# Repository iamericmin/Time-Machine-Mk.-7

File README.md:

# Time-Machine-Mk.-7
Eagle files for the Time Machine Mk. 7, a DIY digital watch powered by a SAMD21 and an LIR2032 battery.

# Repo map
1. Cutting board: failed projects, simple mockups, etc. that didn't make it to the final product
2. Technical drawings: PDFs of TM7 Rev G, the final production version.
3. TM7 older versions: previous revisions of TM7 I kept just cuz

# This only contains hardware files, I'll be working and uploading software here as well soon!

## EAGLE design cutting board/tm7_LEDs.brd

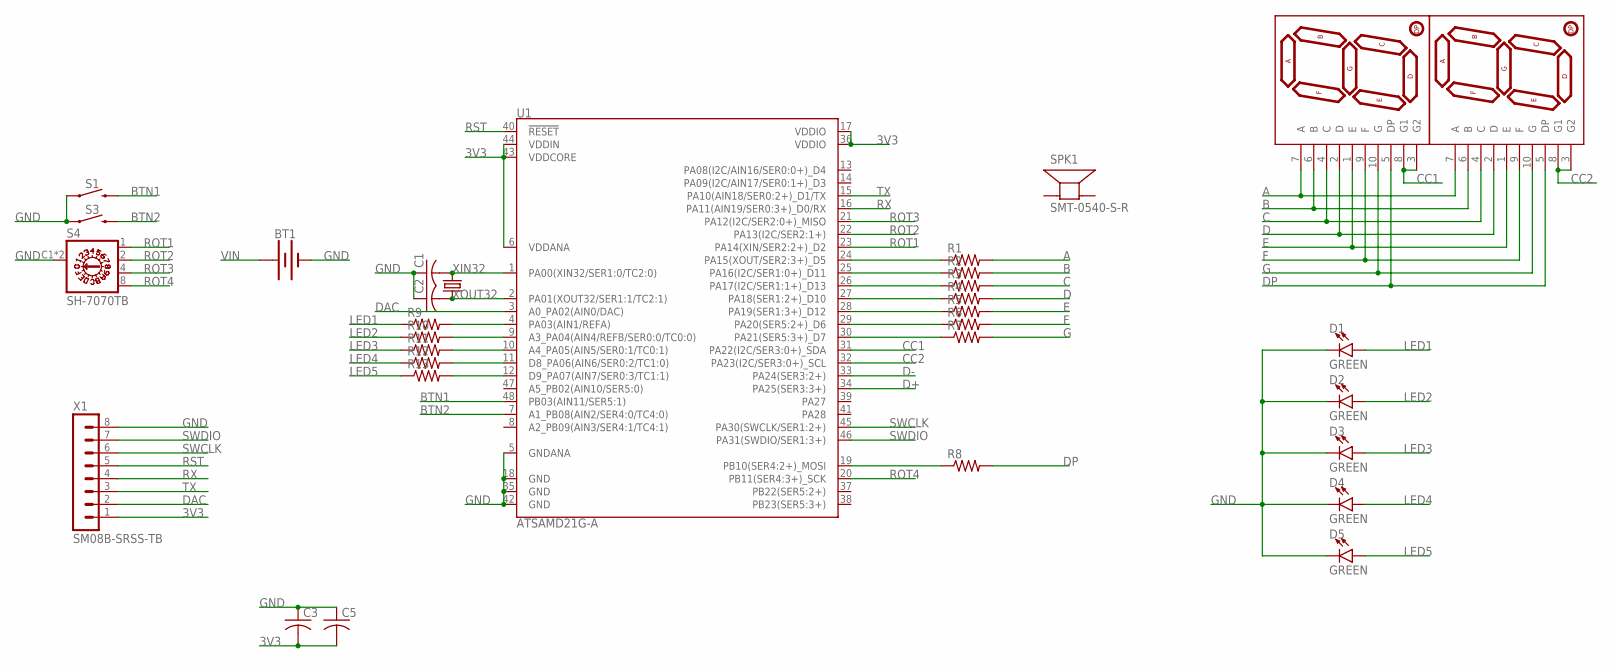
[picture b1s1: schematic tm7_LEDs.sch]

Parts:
BT1: BATTERY-20MM_SMD_4LEGS_OVERPASTE_INNER; BATTCON_20MM_4LEGS_OVERPASTE_INNER
C1, C2, C3, C5: C-USC0603; C0603
D1, D2, D3, D4, D5: GREEN; LED-1206
R1, R2, R3, R4, R5, R6, R7, R8, R9, R10, R11, R12, R13: R-US_R0603; R0603
S1, S3: MOMENTARY-SWITCH-SPST-SMD-6.2MM-TALL; TACTILE_SWITCH_SMD_6.2MM_TALL
S4: SH-7070TB; SH-7070B
SPK1: SMT-0540-S-R
U1: ATSAMD21G-A; TQFP-48
U$2, U$3: 7-SEGMENT-DISPLAY-1"-RED; 7-SEGMENT-SMD
X1: SM08B-SRSS-TB
Y1: 32.768kHz; CRYSTAL-SMD-3.2X1.5MM

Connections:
3V3: C3.2, C5.2, U1.6 (VDDANA), U1.17 (VDDIO), U1.36 (VDDIO), U1.43 (VDDCORE), U1.44 (VDDIN), X1.1
A: R1.2, U$2.7 (A), U$3.7 (A)
B: R2.2, U$2.6 (B), U$3.6 (B)
BTN1: S1.B2 (2), U1.48 (PB03(AIN11/SER5:1))
BTN2: S3.B2 (2), U1.7 (A1_PB08(AIN2/SER4:0/TC4:0))
C: R3.2, U$2.4 (C), U$3.4 (C)
CC1: U1.31 (PA22(I2C/SER3:0+)_SDA), U$2.3 (G2), U$2.8 (G1)
CC2: U1.32 (PA23(I2C/SER3:0+)_SCL), U$3.3 (G2), U$3.8 (G1)
D: R4.2, U$2.2 (D), U$3.2 (D)
D+: U1.34 (PA25(SER3:3+))
D-: U1.33 (PA24(SER3:2+))
DAC: U1.3 (A0_PA02(AIN0/DAC)), X1.2
DP: R8.2, U$2.5 (DP), U$3.5 (DP)
E: R5.2, U$2.1 (E), U$3.1 (E)
F: R6.2, U$2.9 (F), U$3.9 (F)
G: R7.2, U$2.10 (G), U$3.10 (G)
GND: BT1.2 (-), C1.1, C2.1, C3.1, C5.1, D1.C, D2.C, D3.C, D4.C, D5.C, S1.A2 (1), S3.A2 (1), S4.C1 (C), S4.C2 (C), U1.5 (GNDANA), U1.18 (GND), U1.35 (GND), U1.42 (GND), X1.8
LED1: D1.A, R9.1
LED2: D2.A, R10.1
LED3: D3.A, R11.1
LED4: D4.A, R12.1
LED5: D5.A, R13.1
unnamed: R1.1, U1.24 (PA15(XOUT/SER2:3+)_D5)
unnamed: R2.1, U1.25 (PA16(I2C/SER1:0+)_D11)
unnamed: R3.1, U1.26 (PA17(I2C/SER1:1+)_D13)
unnamed: R4.1, U1.27 (PA18(SER1:2+)_D10)
unnamed: R5.1, U1.28 (PA19(SER1:3+)_D12)
unnamed: R7.1, U1.30 (PA21(SER5:3+)_D7)
unnamed: R6.1, U1.29 (PA20(SER5:2+)_D6)
unnamed: R8.1, U1.19 (PB10(SER4:2+)_MOSI)
unnamed: R9.2, U1.4 (PA03(AIN1/REFA))
unnamed: R10.2, U1.9 (A3_PA04(AIN4/REFB/SER0:0/TC0:0))
unnamed: R11.2, U1.10 (A4_PA05(AIN5/SER0:1/TC0:1))
unnamed: R12.2, U1.11 (D8_PA06(AIN6/SER0:2/TC1:0))
unnamed: R13.2, U1.12 (D9_PA07(AIN7/SER0:3/TC1:1))
ROT1: S4.1, U1.23 (PA14(XIN/SER2:2+)_D2)
ROT2: S4.2, U1.22 (PA13(I2C/SER2:1+))
ROT3: S4.4, U1.21 (PA12(I2C/SER2:0+)_MISO)
ROT4: S4.8, U1.20 (PB11(SER4:3+)_SCK)
RST: U1.40 (!RESET!), X1.5
RX: U1.16 (PA11(AIN19/SER0:3+)_D0/RX), X1.4
SWCLK: U1.45 (PA30(SWCLK/SER1:2+)), X1.6
SWDIO: U1.46 (PA31(SWDIO/SER1:3+)), X1.7
TX: U1.15 (PA10(AIN18/SER0:2+)_D1/TX), X1.3
VIN: BT1.1 (+)
XIN32: C1.2, U1.1 (PA00(XIN32/SER1:0/TC2:0)), Y1.P$2 (2)
XOUT32: C2.2, U1.2 (PA01(XOUT32/SER1:1/TC2:1)), Y1.P$1 (1)

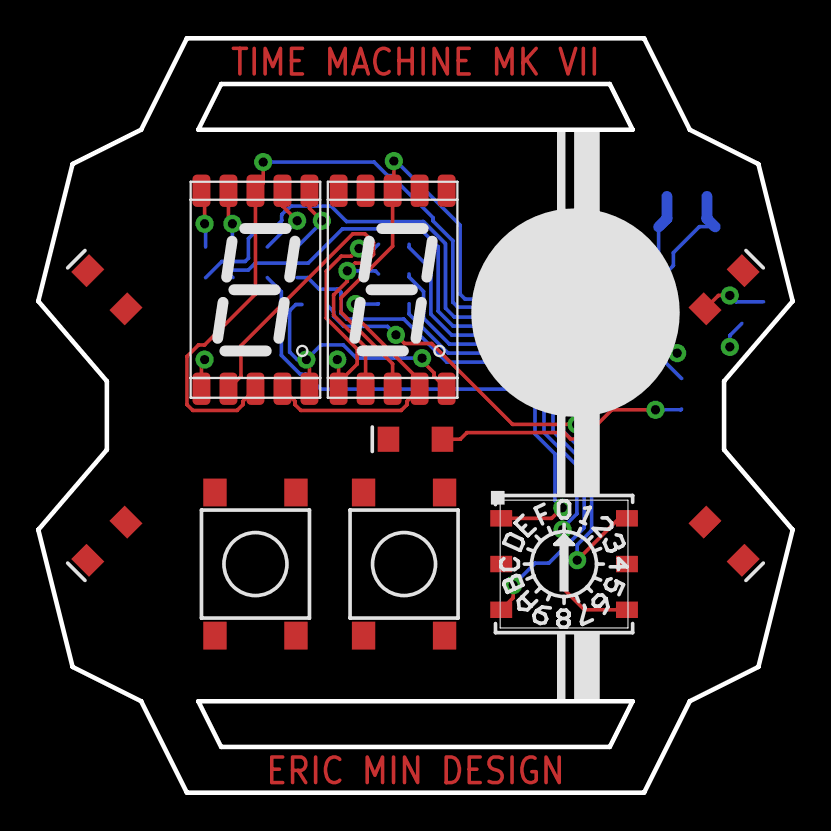
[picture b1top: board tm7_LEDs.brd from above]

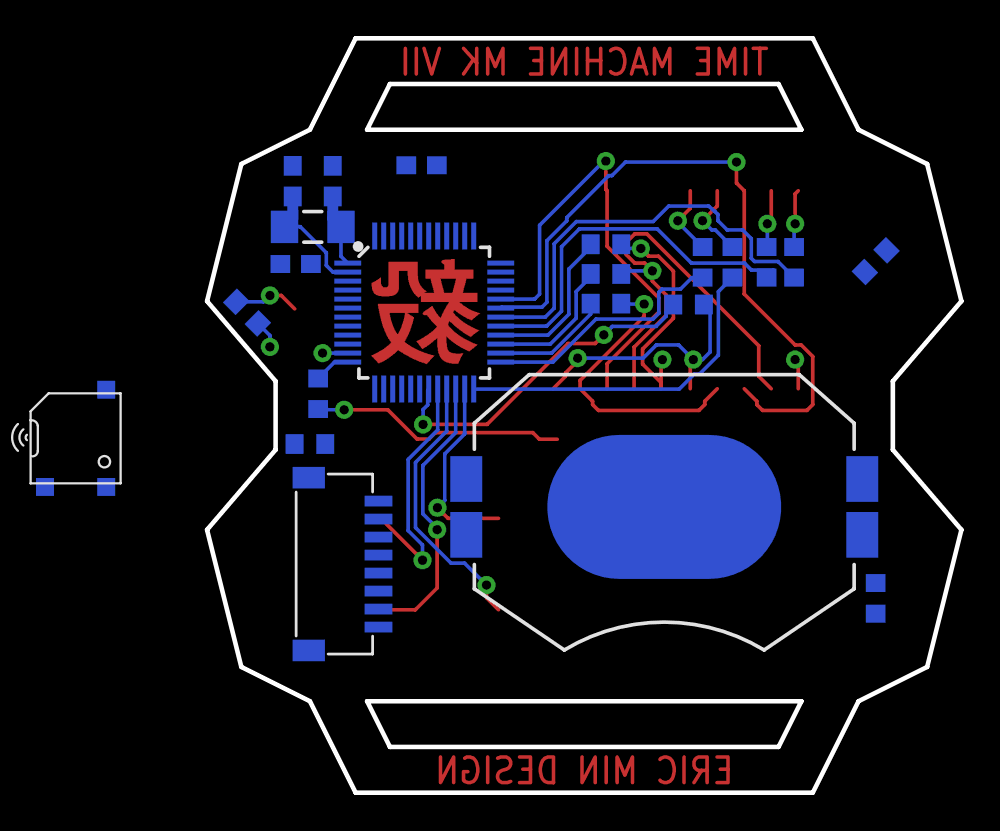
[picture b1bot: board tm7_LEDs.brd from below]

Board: 4 copper layers, 41.9 x 41.9 mm, 32 parts (22 on the bottom side), 44 nets.

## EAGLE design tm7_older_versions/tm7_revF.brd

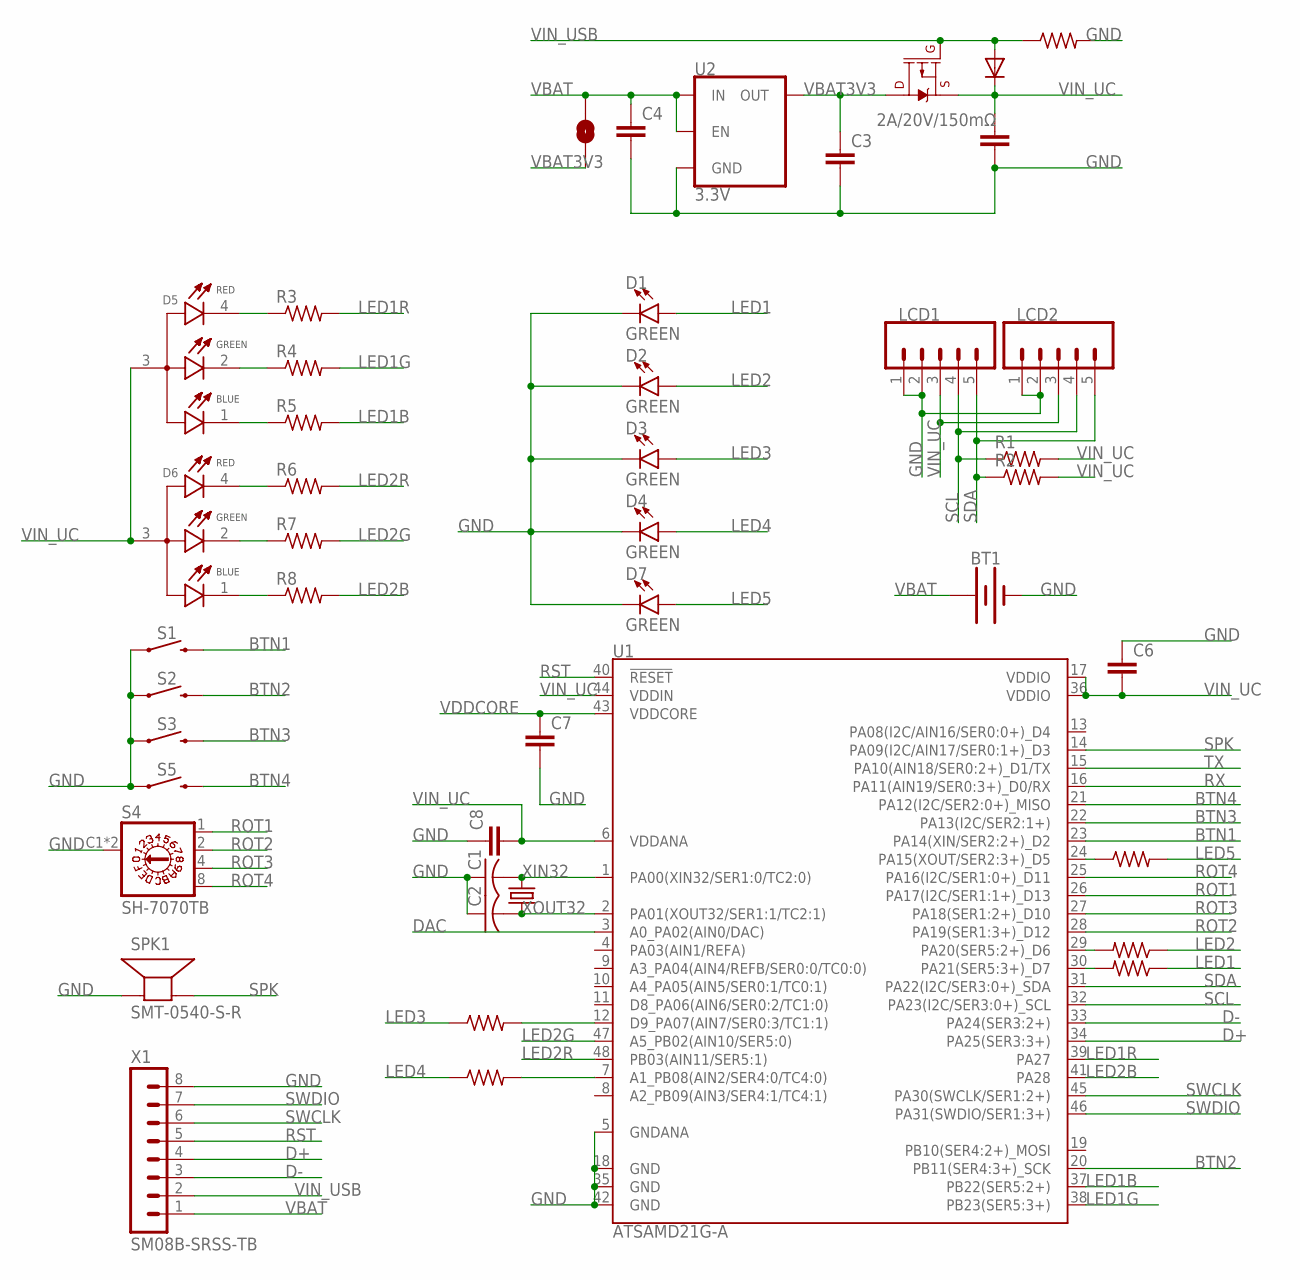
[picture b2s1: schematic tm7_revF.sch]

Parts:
BT1: BATTERY-20MM_SMD_4LEGS_OVERPASTE_INNER; BATTCON_20MM_4LEGS_OVERPASTE_INNER
C1, C2: C-USC0603; C0603
C3, C4, C6, C7, C8, C9: C-EUC0603; C0603
D1, D2, D3, D4, D7: GREEN; LED-1206
D5, D6: EAST1616RGBA3; LED_EAST1616RGBA3
D8: DIODESOD-323F; SOD-323F
JP1: JUMPER-SMT_2_NO_NO-SILK; SMT-JUMPER_2_NO_NO-SILK
LCD1, LCD2: CONN_05VERT_FEMALE_HEADER; 1X05_SMD_VERTICAL_COMBO
Q1: 2A/20V/150mΩ; SOT26
R1, R2, R3, R4, R5, R6, R7, R8, R9, R10, R11, R12, R13, R14: R-US_R0603; R0603
S1, S2, S3, S5: MOMENTARY-SWITCH-SPST-SMD-6.0X3.5MM; TACTILE_SWITCH_SMD_6.0X3.5MM
S4: SH-7070TB; SH-7070B
SPK1: SMT-0540-S-R
U1: ATSAMD21G-A; TQFP-48
U2: 3.3V; SOT23-5
X1: SM08B-SRSS-TB
Y1: 32.768kHz; CRYSTAL-SMD-3.2X1.5MM

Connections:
BTN1: S1.2, U1.23 (PA14(XIN/SER2:2+)_D2)
BTN2: S2.2, U1.20 (PB11(SER4:3+)_SCK)
BTN3: S3.2, U1.22 (PA13(I2C/SER2:1+))
BTN4: S5.2, U1.21 (PA12(I2C/SER2:0+)_MISO)
D+: U1.34 (PA25(SER3:3+)), X1.4
D-: U1.33 (PA24(SER3:2+)), X1.3
DAC: U1.3 (A0_PA02(AIN0/DAC))
GND: BT1.2 (-), C1.1, C2.1, C3.2, C4.2, C6.1, C7.2, C8.1, C9.2, D1.C, D2.C, D3.C, D4.C, D7.C, LCD1.1, LCD1.2, LCD2.1, LCD2.2, R14.2, S1.1, S2.1, S3.1, S4.C1 (C), S4.C2 (C), S5.1, SPK1.- (+), U1.5 (GNDANA), U1.18 (GND), U1.35 (GND), U1.42 (GND), U2.2 (GND), X1.8
LED1: D1.A, R9.1
LED1B: R5.2, U1.37 (PB22(SER5:2+))
LED1G: R4.2, U1.38 (PB23(SER5:3+))
LED1R: R3.2, U1.39 (PA27)
LED2: D2.A, R10.1
LED2B: R8.2, U1.41 (PA28)
LED2G: R7.2, U1.47 (A5_PB02(AIN10/SER5:0))
LED2R: R6.2, U1.48 (PB03(AIN11/SER5:1))
LED3: D3.A, R11.1
LED4: D4.A, R12.1
LED5: D7.A, R13.2
unnamed: R12.2, U1.7 (A1_PB08(AIN2/SER4:0/TC4:0))
unnamed: R11.2, U1.12 (D9_PA07(AIN7/SER0:3/TC1:1))
unnamed: R9.2, U1.30 (PA21(SER5:3+)_D7)
unnamed: R10.2, U1.29 (PA20(SER5:2+)_D6)
unnamed: D5.4 (R_C), R3.1
unnamed: D5.2 (G_C), R4.1
unnamed: D5.1 (B_C), R5.1
unnamed: D6.4 (R_C), R6.1
unnamed: D6.2 (G_C), R7.1
unnamed: D6.1 (B_C), R8.1
unnamed: R13.1, U1.24 (PA15(XOUT/SER2:3+)_D5)
ROT1: S4.1, U1.26 (PA17(I2C/SER1:1+)_D13)
ROT2: S4.2, U1.28 (PA19(SER1:3+)_D12)
ROT3: S4.4, U1.27 (PA18(SER1:2+)_D10)
ROT4: S4.8, U1.25 (PA16(I2C/SER1:0+)_D11)
RST: U1.40 (!RESET!), X1.5
RX: U1.16 (PA11(AIN19/SER0:3+)_D0/RX)
SCL: LCD1.4, LCD2.4, R1.1, U1.32 (PA23(I2C/SER3:0+)_SCL)
SDA: LCD1.5, LCD2.5, R2.1, U1.31 (PA22(I2C/SER3:0+)_SDA)
SPK: SPK1.+ (-), U1.14 (PA09(I2C/AIN17/SER0:1+)_D3)
SWCLK: U1.45 (PA30(SWCLK/SER1:2+)), X1.6
SWDIO: U1.46 (PA31(SWDIO/SER1:3+)), X1.7
TX: U1.15 (PA10(AIN18/SER0:2+)_D1/TX)
VBAT: BT1.1 (+), C4.1, JP1.2, U2.1 (IN), U2.3 (EN), X1.1
VBAT3V3: C3.1, JP1.1, Q1.D1 (D), U2.5 (OUT)
VDDCORE: C7.1, U1.43 (VDDCORE)
VIN_UC: C6.2, C8.2, C9.1, D5.3 (A), D6.3 (A), D8.C, LCD1.3, LCD2.3, Q1.S1 (S), R1.2, R2.2, U1.6 (VDDANA), U1.17 (VDDIO), U1.36 (VDDIO), U1.44 (VDDIN)
VIN_USB: D8.A, Q1.G1 (G), R14.1, X1.2
XIN32: C1.2, U1.1 (PA00(XIN32/SER1:0/TC2:0)), Y1.P$2 (2)
XOUT32: C2.2, U1.2 (PA01(XOUT32/SER1:1/TC2:1)), Y1.P$1 (1)

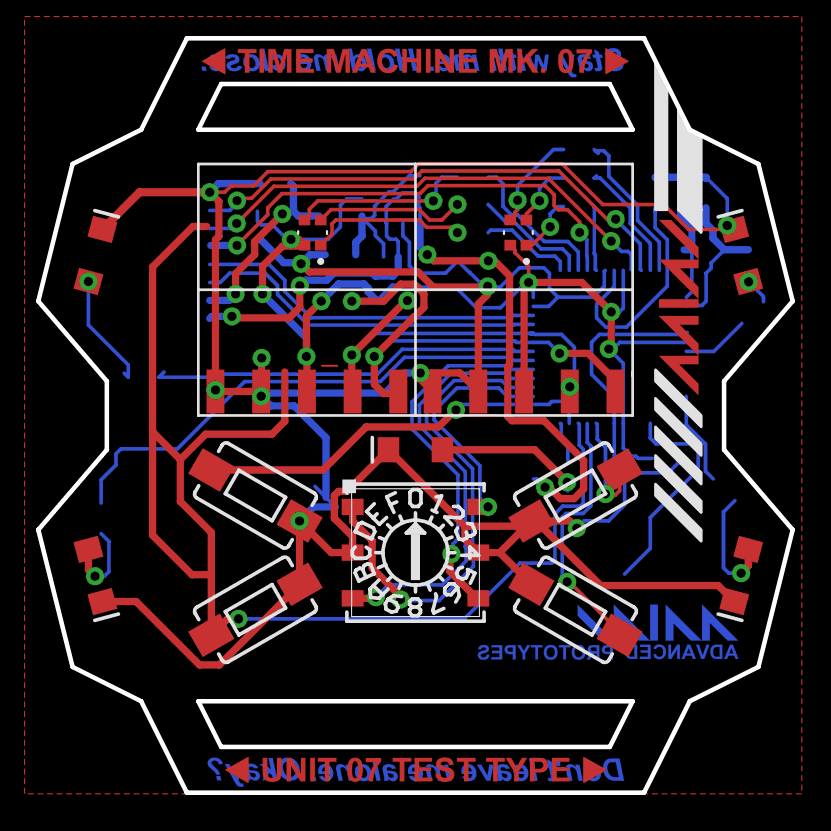
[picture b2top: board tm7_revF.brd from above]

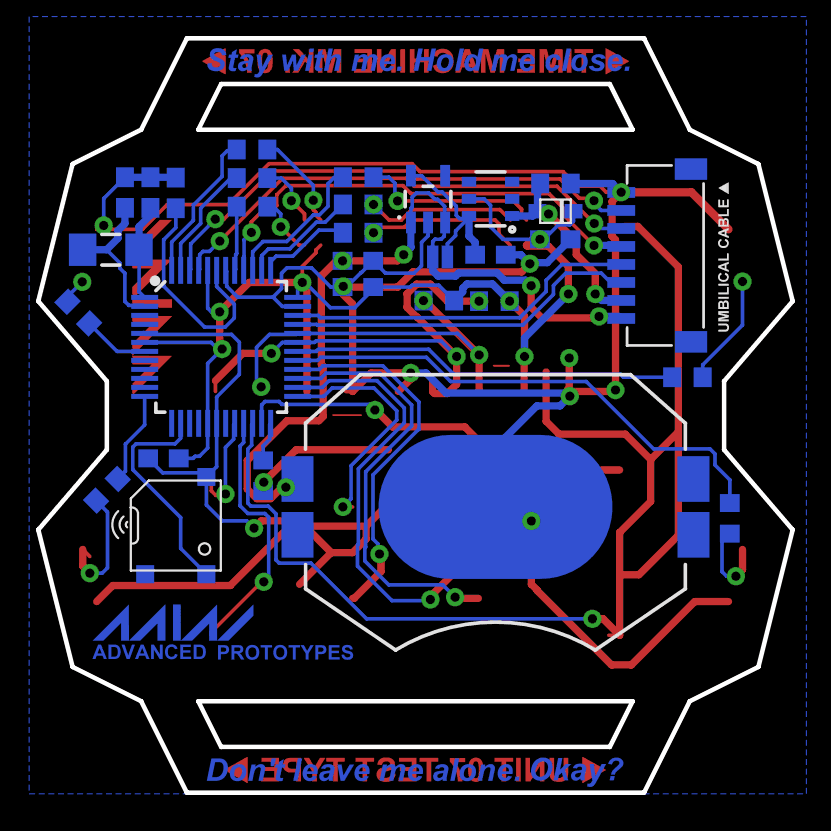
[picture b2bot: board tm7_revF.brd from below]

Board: 2 copper layers, 41.9 x 41.9 mm, 45 parts (31 on the bottom side), 46 nets.

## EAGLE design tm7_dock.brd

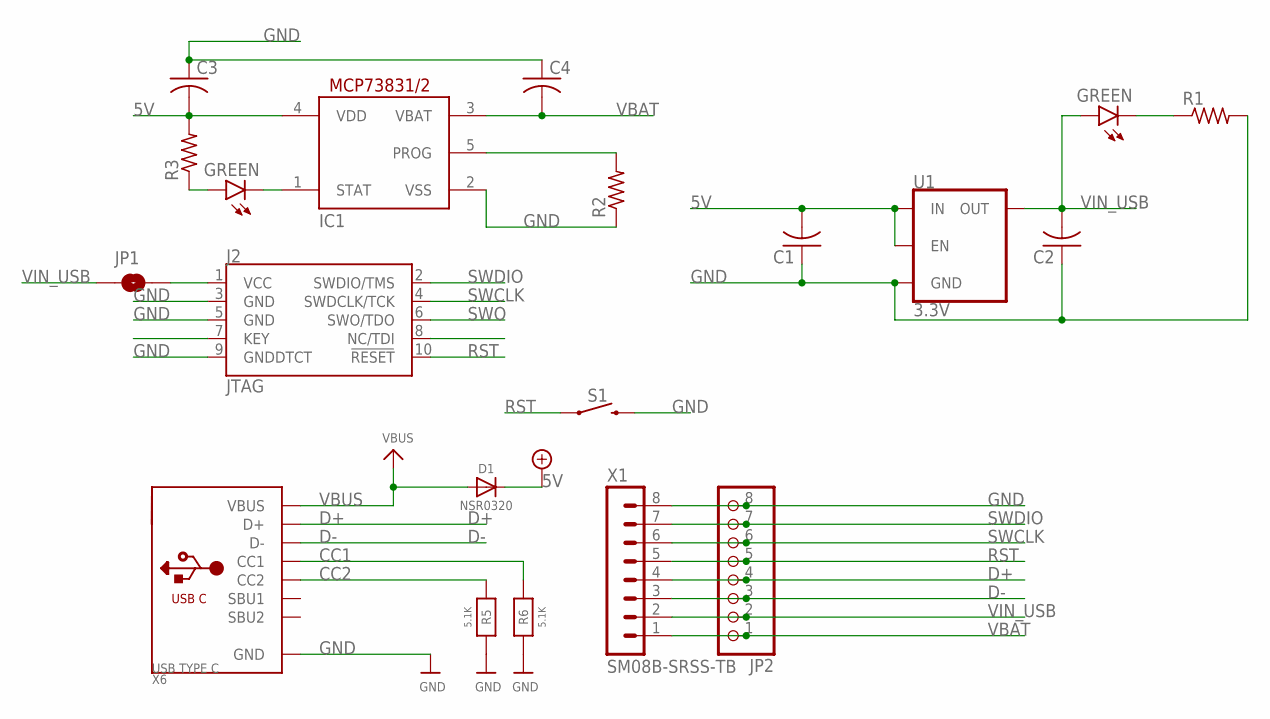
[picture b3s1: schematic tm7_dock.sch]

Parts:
C1, C2, C3, C4: C-USC0603; C0603
D1: NSR0320; SOD-323_MINI
D2, D3: GREEN; LED-1206
IC1: MCP73831/OT; SOT23-5L
J2: JTAG; 2X5-SMD-1.27MM
JP1: JUMPER-SMT_2_NO_NO-SILK; SMT-JUMPER_2_NO_NO-SILK
JP2: PINHD-1X8LOCK; 1X08-LOCK
R1, R2, R3: R-US_R0603; R0603
R5, R6: 5.1K; _0402NO
S1: MOMENTARY-SWITCH-SPST-SMD-5.2MM-TALL; TACTILE_SWITCH_SMD_5.2MM
U1: 3.3V; SOT23-5
X1: SM08B-SRSS-TB
X6: USB TYPE C; USB_C_CUSB31-CFM2AX-01-X

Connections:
5V: C1.2, C3.2, D1.C, IC1.4 (VDD), R3.2, U1.1 (IN), U1.3 (EN)
CC1: R6.2, X6.A5 (CC1)
CC2: R5.2, X6.B5 (CC2)
D+: JP2.4, X1.4, X6.A6 (D+), X6.B6 (D+)
D-: JP2.3, X1.3, X6.A7 (D-), X6.B7 (D-)
GND: C1.1, C2.1, C3.1, C4.1, IC1.2 (VSS), J2.3 (GND), J2.5 (GND), J2.9 (GNDDTCT), JP2.8, R1.2, R2.1, R5.1, R6.1, S1.3 (2), U1.2 (GND), X1.8, X6.A1B12 (GND), X6.B1A12 (GND)
unnamed: D2.C, R1.1
unnamed: IC1.5 (PROG), R2.2
unnamed: D3.C, IC1.1 (STAT)
unnamed: D3.A, R3.1
unnamed: J2.1 (VCC), JP1.2
RST: J2.10 (!RESET), JP2.5, S1.1, X1.5
SWCLK: J2.4 (SWDCLK/TCK), JP2.6, X1.6
SWDIO: J2.2 (SWDIO/TMS), JP2.7, X1.7
SWO: J2.6 (SWO/TDO)
VBAT: C4.2, IC1.3 (VBAT), JP2.1, X1.1
VBUS: D1.A, X6.A4B9 (VBUS), X6.B4A9 (VBUS)
VIN_USB: C2.2, D2.A, JP1.1, JP2.2, U1.5 (OUT), X1.2

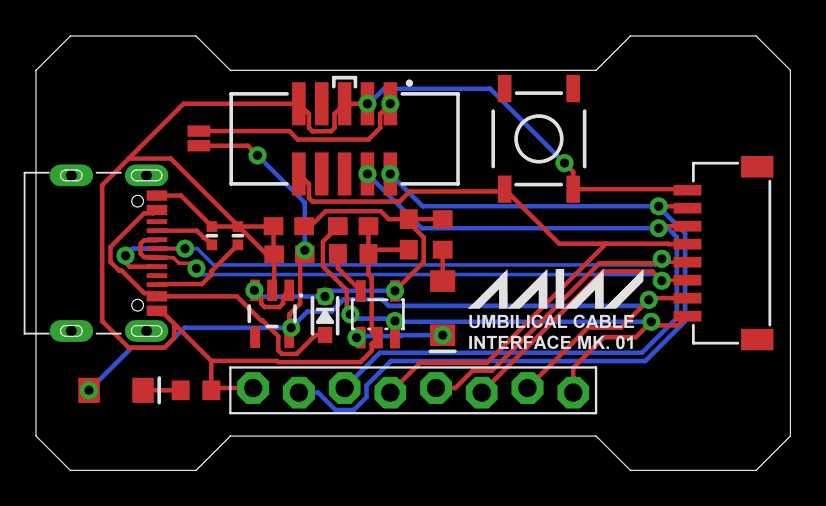
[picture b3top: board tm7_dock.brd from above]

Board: 2 copper layers, 41.9 x 24.1 mm, 20 parts (0 on the bottom side), 17 nets.

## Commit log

2023-04-08 very minor tweaks, backup really

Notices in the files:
parts and their libraries:
SparkFun-Switches: Licensing: Creative Commons ShareAlike 4.0 International - https://creativecommons.org/licenses/by-sa/4.0
microbuilder: This work is placed in the public domain, and may be freely used for commercial and non-commercial work with the following conditions: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
